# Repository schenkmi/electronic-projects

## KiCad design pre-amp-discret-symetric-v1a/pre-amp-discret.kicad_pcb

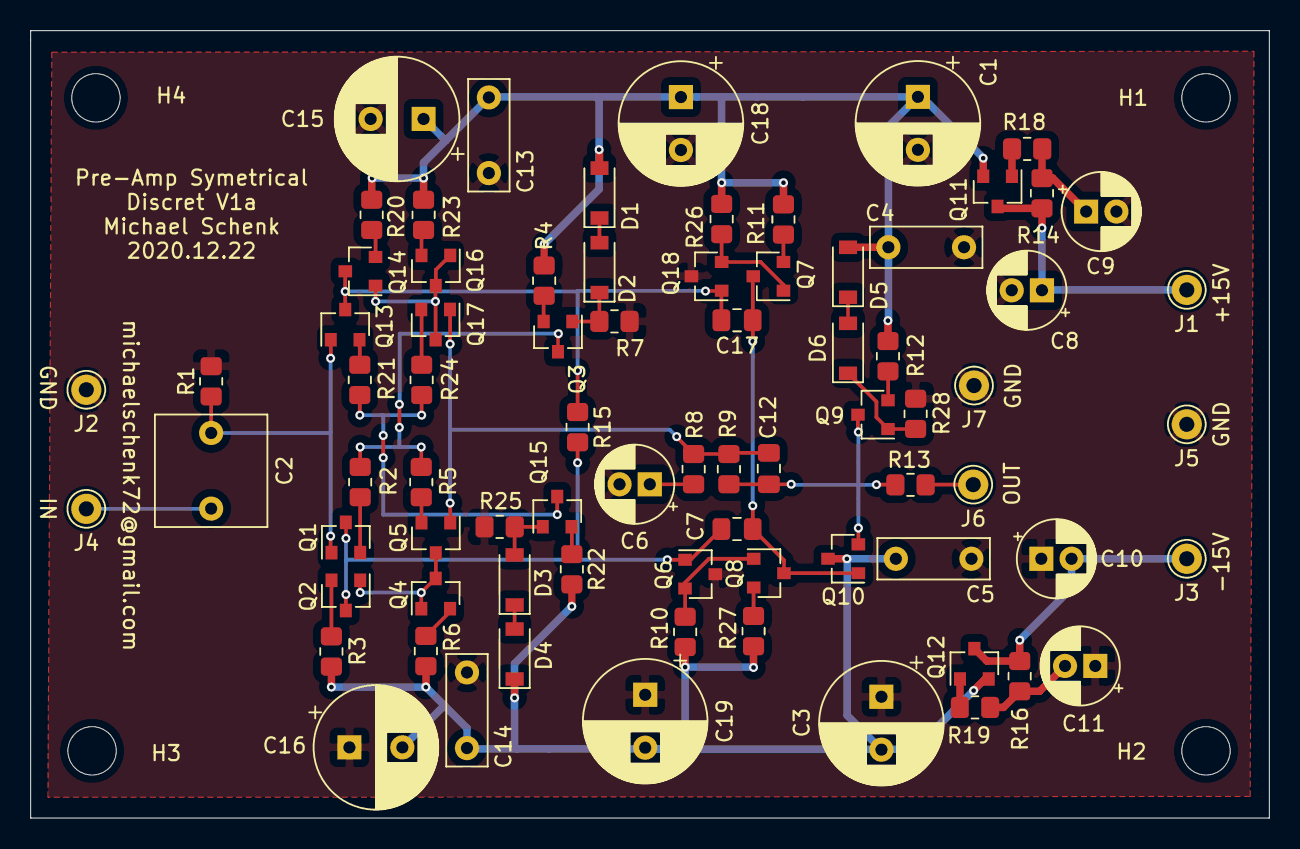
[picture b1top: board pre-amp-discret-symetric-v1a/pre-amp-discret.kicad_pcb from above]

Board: 2 copper layers, 81.9 x 52.1 mm, 81 parts (0 on the bottom side), 43 nets.

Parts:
C1, C3, C15, C16, C18, C19: 220uF; CP_Radial_D8.0mm_P3.50mm
C2: 2.2uF; C_Rect_L7.2mm_W7.2mm_P5.00mm_FKS2_FKP2_MKS2_MKP2
C4, C5, C13, C14: 100nF; C_Rect_L7.2mm_W2.5mm_P5.00mm_FKS2_FKP2_MKS2_MKP2
C6, C8, C9, C10, C11: 100uF; CP_Radial_D5.0mm_P2.00mm
C7, C17: 1nF; C_0805_2012Metric_Pad1.18x1.45mm_HandSolder
C12: 4.7pF; C_0805_2012Metric_Pad1.18x1.45mm_HandSolder
D1, D2, D3, D4, D5, D6: 1N4148W; D_SOD-123
H1, H2, H3, H4: MountingHole; MountingHole_3.2mm_M3
J1, J2, J3, J4, J5, J6, J7: Conn_01x01; Pin_D1.0mm_L10.0mm
Q1, Q3, Q5, Q7, Q9, Q10, Q12, Q14, Q16, Q18: BC860C; SOT-23
Q2, Q4, Q6, Q8, Q11, Q13, Q15, Q17: BC850C; SOT-23
R1, R8, R9: 22k; R_0805_2012Metric_Pad1.20x1.40mm_HandSolder
R2, R5, R12, R18, R19, R21, R24: 100R; R_0805_2012Metric_Pad1.20x1.40mm_HandSolder
R3, R6, R20, R23: 68R; R_0805_2012Metric_Pad1.20x1.40mm_HandSolder
R4, R22: 150R; R_0805_2012Metric_Pad1.20x1.40mm_HandSolder
R7, R14, R16, R25, R28: 10k; R_0805_2012Metric_Pad1.20x1.40mm_HandSolder
R10, R26: 2k2; R_0805_2012Metric_Pad1.20x1.40mm_HandSolder
R11, R27: 39R; R_0805_2012Metric_Pad1.20x1.40mm_HandSolder
R13: 47R; R_0805_2012Metric_Pad1.20x1.40mm_HandSolder
R15: 250k; R_0805_2012Metric_Pad1.20x1.40mm_HandSolder

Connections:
+15V: C1.1, C4.2, C13.2, C15.1, C18.1, D1.2, D5.2, Q11.2, R4.1, R11.1, R12.1, R20.1, R23.1, R26.1
-15V: C3.2, C5.1, C14.1, C16.2, C19.2, D4.1, Q10.3, Q12.2, R3.2, R6.2, R10.2, R22.2, R27.2
GND: C1.2, C3.1, C4.1, C5.2, C6.2, C8.2, C9.2, C10.1, C11.1, C13.1, C14.2, C15.2, C16.1, C18.2, C19.1, J2.1, J5.1, J7.1, Q6.3, Q18.3, R1.2, R7.2, R25.1, R28.2
unnamed: C2.1, Q1.1, Q13.1, R1.1
unnamed: C2.2, J4.1
unnamed: C6.1, R8.2
unnamed: C7.2, Q1.3, Q2.3, Q6.1, R15.2
unnamed: C8.1, J1.1, Q11.3, R14.2
unnamed: C9.1, R14.1, R18.1
unnamed: C10.2, J3.1, Q12.3, R16.2
unnamed: C11.2, R16.1, R19.1
unnamed: C12.1, Q9.3, Q10.2, R9.1, R13.2
unnamed: C12.2, Q5.1, Q17.1, R8.1, R9.2
unnamed: C7.1, C17.1, Q7.3, Q8.3, Q10.1
unnamed: C17.2, Q13.3, Q14.3, Q18.1, R15.1
unnamed: D1.1, D2.2
unnamed: D2.1, Q3.1, R7.1
unnamed: D3.1, D4.2
unnamed: D3.2, Q15.1, R25.2
unnamed: D5.1, D6.2
unnamed: D6.1, Q9.1, R28.1
unnamed: J6.1, R13.1
unnamed: Q1.2, R2.2
unnamed: Q2.1, Q4.1, Q4.3, Q5.3
unnamed: Q2.2, R3.1
unnamed: Q3.2, R4.2
unnamed: Q3.3, R2.1, R5.1
unnamed: Q4.2, R6.1
unnamed: Q5.2, R5.2
unnamed: Q6.2, Q8.1, R10.1
unnamed: Q7.2, R11.2
unnamed: Q8.2, R27.1
unnamed: Q9.2, R12.2
unnamed: Q11.1, R18.2
unnamed: Q12.1, R19.2
unnamed: Q13.2, R21.1
unnamed: Q14.1, Q16.1, Q16.3, Q17.3
unnamed: Q14.2, R20.2
unnamed: Q15.2, R22.1
unnamed: Q15.3, R21.2, R24.2
unnamed: Q16.2, R23.2
unnamed: Q17.2, R24.1
unnamed: Q7.1, Q18.2, R26.2

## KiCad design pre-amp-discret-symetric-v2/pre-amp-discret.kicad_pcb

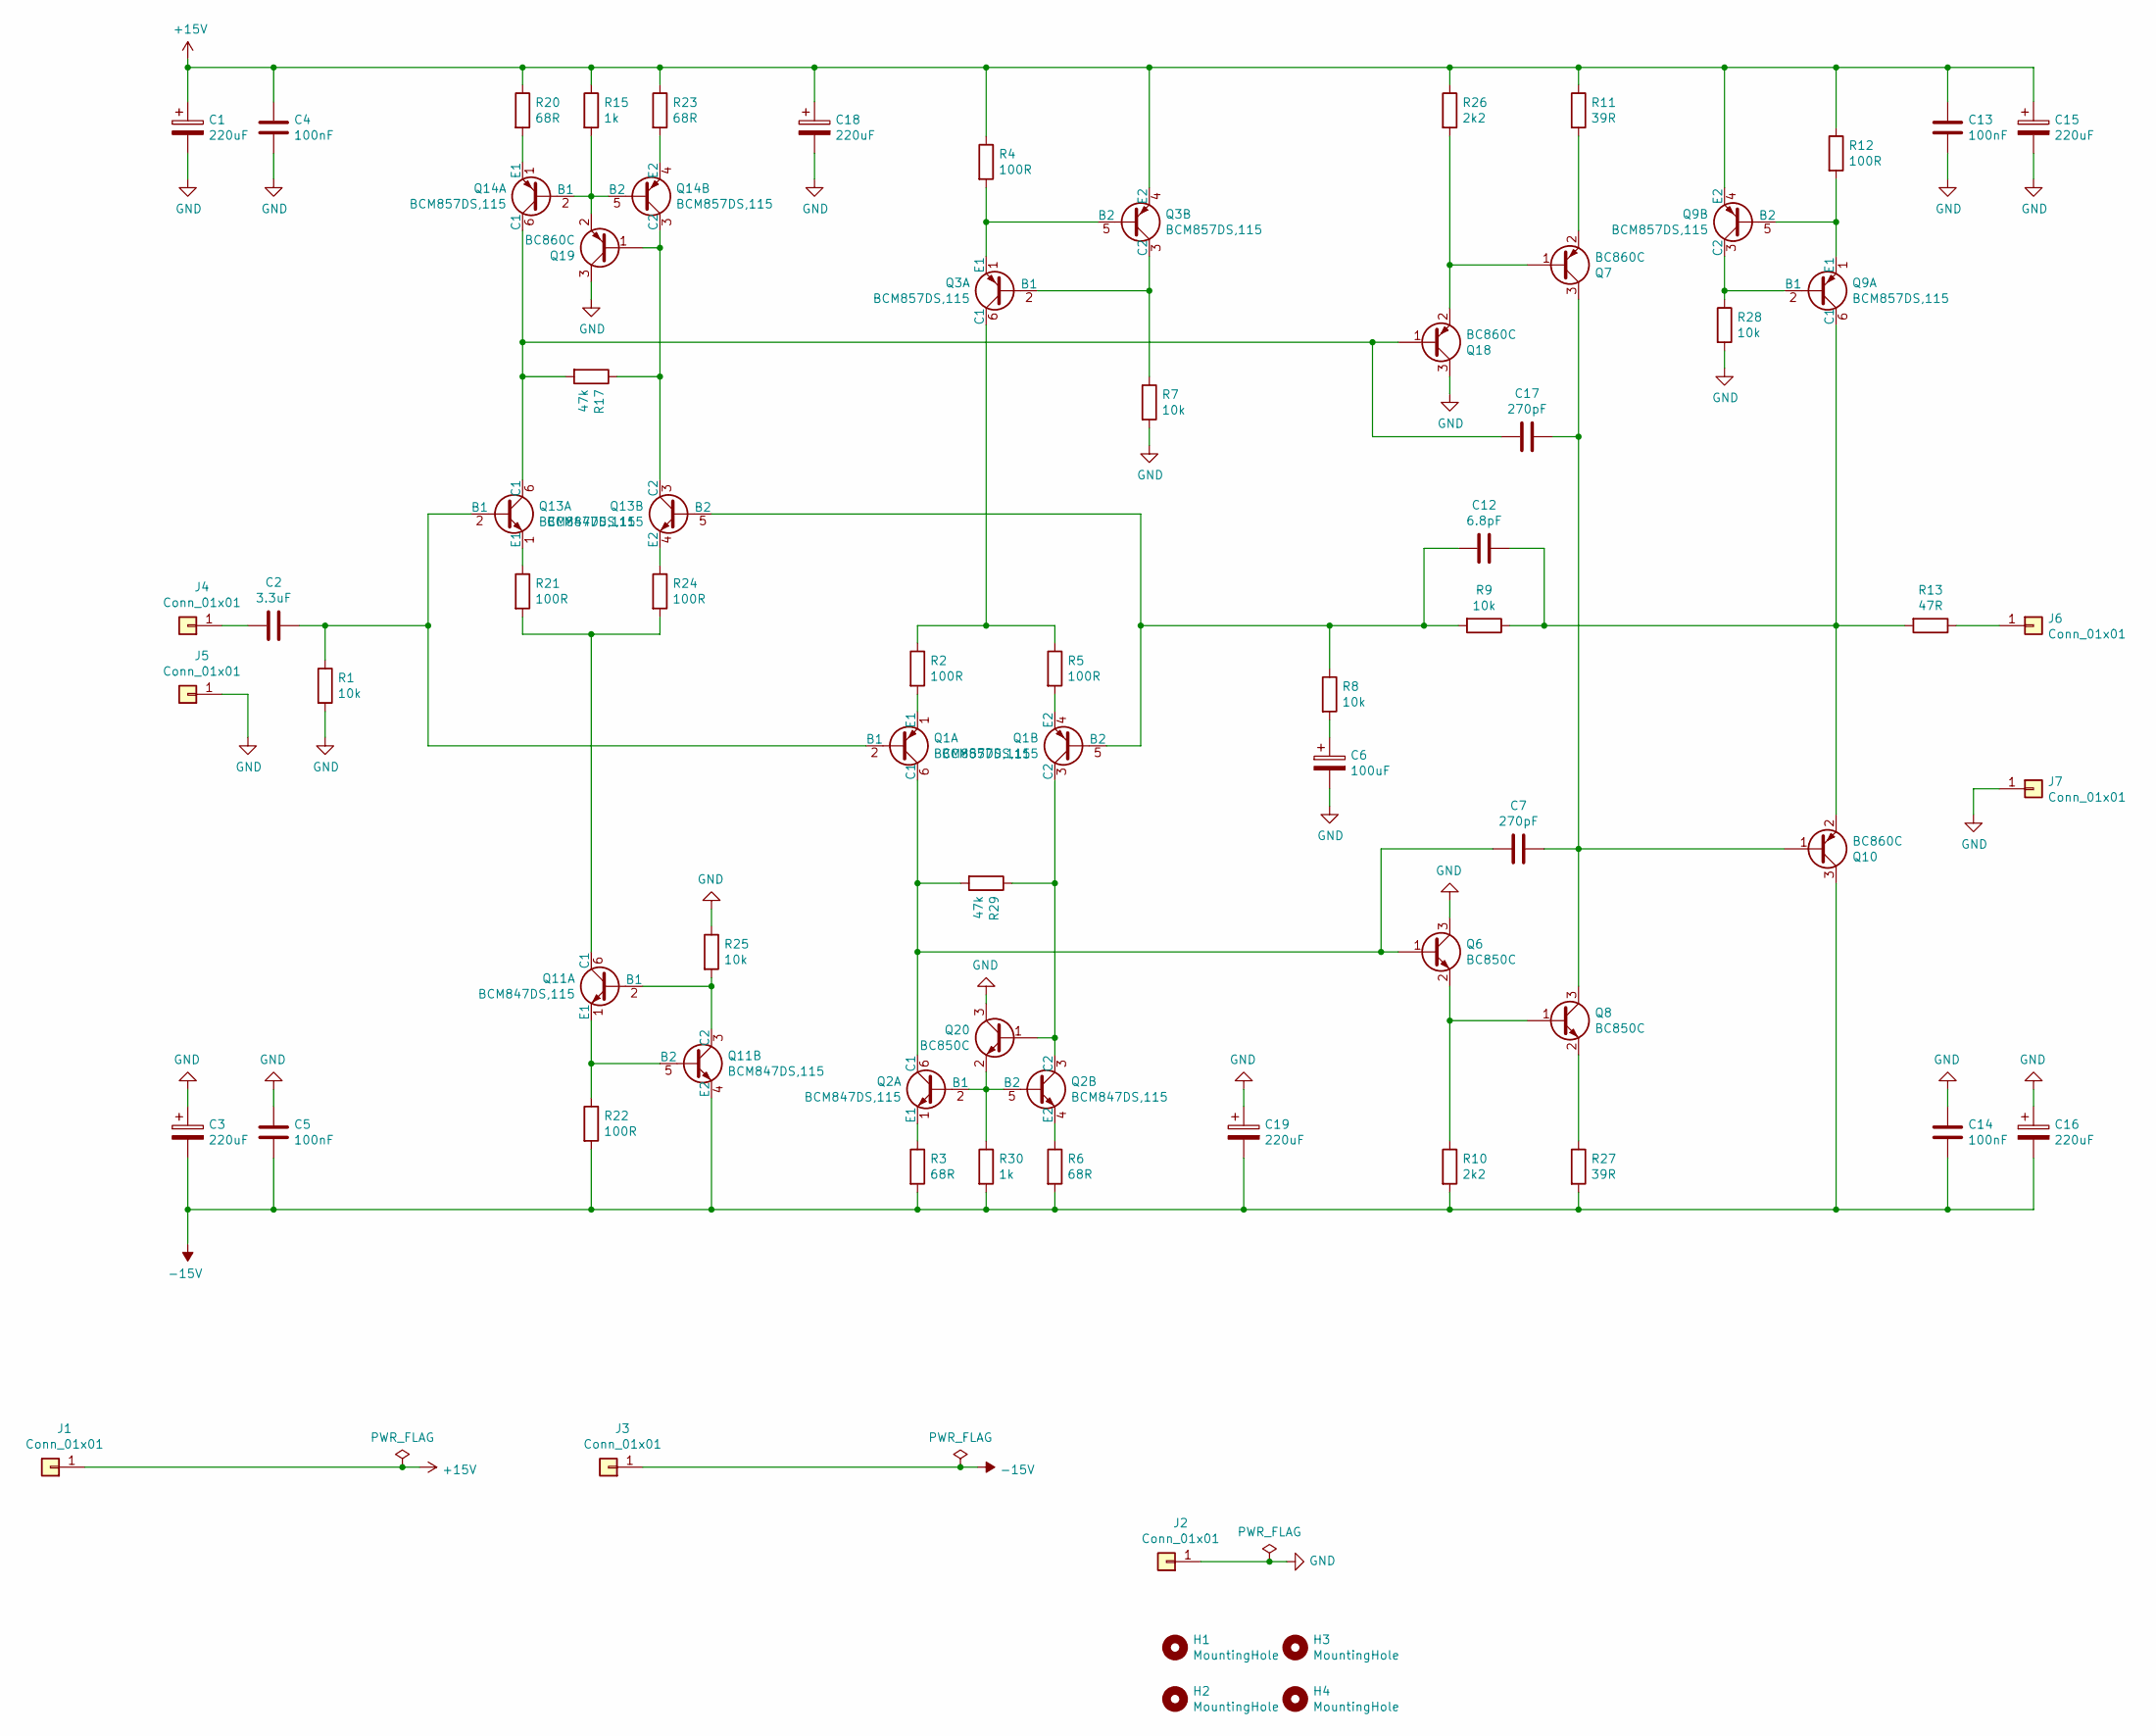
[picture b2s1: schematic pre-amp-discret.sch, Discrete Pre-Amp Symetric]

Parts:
C1, C3, C15, C16, C18, C19: 220uF; CP_Radial_D8.0mm_P3.50mm
C2: 3.3uF; C_Rect_L7.2mm_W7.2mm_P5.00mm_FKS2_FKP2_MKS2_MKP2
C4, C5, C13, C14: 100nF; C_Rect_L7.2mm_W2.5mm_P5.00mm_FKS2_FKP2_MKS2_MKP2
C6: 100uF; CP_Radial_D5.0mm_P2.00mm
C7, C17: 270pF; C_0805_2012Metric_Pad1.18x1.45mm_HandSolder
C12: 6.8pF; C_0805_2012Metric_Pad1.18x1.45mm_HandSolder
H1, H2, H3, H4: MountingHole; MountingHole_3.2mm_M3
J1, J2, J3, J4, J5, J6, J7: Conn_01x01; Pin_D1.0mm_L10.0mm
Q1, Q3, Q9, Q14: BCM857DS,115; SC-74-6_1.5x2.9mm_P0.95mm
Q2, Q11, Q13: BCM847DS,115; SC-74-6_1.5x2.9mm_P0.95mm
Q6, Q8, Q20: BC850C; SOT-23
Q7, Q10, Q18, Q19: BC860C; SOT-23
R1, R7, R8, R9, R25, R28: 10k; R_0805_2012Metric_Pad1.20x1.40mm_HandSolder
R2, R4, R5, R12, R21, R22, R24: 100R; R_0805_2012Metric_Pad1.20x1.40mm_HandSolder
R3, R6, R20, R23: 68R; R_0805_2012Metric_Pad1.20x1.40mm_HandSolder
R10, R26: 2k2; R_0805_2012Metric_Pad1.20x1.40mm_HandSolder
R11, R27: 39R; R_0805_2012Metric_Pad1.20x1.40mm_HandSolder
R13: 47R; R_0805_2012Metric_Pad1.20x1.40mm_HandSolder
R15, R30: 1k; R_0805_2012Metric_Pad1.20x1.40mm_HandSolder
R17, R29: 47k; R_0805_2012Metric_Pad1.20x1.40mm_HandSolder

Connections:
+15V: C1.1, C4.2, C13.2, C15.1, C18.1, J1.1, Q3.4 (E2), Q9.4 (E2), R4.1, R11.1, R12.1, R15.1, R20.1, R23.1, R26.1
-15V: C3.2, C5.1, C14.1, C16.2, C19.2, J3.1, Q10.3 (C), Q11.4 (E2), R3.2, R6.2, R10.2, R22.2, R27.2, R30.2
GND: C1.2, C3.1, C4.1, C5.2, C6.2, C13.1, C14.2, C15.2, C16.1, C18.2, C19.1, J2.1, J5.1, J7.1, Q6.3 (C), Q18.3 (C), Q19.3 (C), Q20.3 (C), R1.2, R7.2, R25.1, R28.2
unnamed: C2.1, Q1.2 (B1), Q13.2 (B1), R1.1
unnamed: C2.2, J4.1
unnamed: C6.1, R8.2
unnamed: C7.2, Q1.6 (C1), Q2.6 (C1), Q6.1 (B), R29.2
unnamed: C12.1, Q9.6 (C1), Q10.2 (E), R9.1, R13.2
unnamed: C12.2, Q1.5 (B2), Q13.5 (B2), R8.1, R9.2
unnamed: C7.1, C17.1, Q7.3 (C), Q8.3 (C), Q10.1 (B)
unnamed: C17.2, Q13.6 (C1), Q14.6 (C1), Q18.1 (B), R17.2
unnamed: J6.1, R13.1
unnamed: Q1.1 (E1), R2.2
unnamed: Q1.3 (C2), Q2.3 (C2), Q20.1 (B), R29.1
unnamed: Q1.4 (E2), R5.2
unnamed: Q2.1 (E1), R3.1
unnamed: Q2.2 (B1), Q2.5 (B2), Q20.2 (E), R30.1
unnamed: Q2.4 (E2), R6.1
unnamed: Q3.1 (E1), Q3.5 (B2), R4.2
unnamed: Q3.2 (B1), Q3.3 (C2), R7.1
unnamed: Q3.6 (C1), R2.1, R5.1
unnamed: Q6.2 (E), Q8.1 (B), R10.1
unnamed: Q7.2 (E), R11.2
unnamed: Q8.2 (E), R27.1
unnamed: Q9.1 (E1), Q9.5 (B2), R12.2
unnamed: Q9.2 (B1), Q9.3 (C2), R28.1
unnamed: Q11.1 (E1), Q11.5 (B2), R22.1
unnamed: Q11.2 (B1), Q11.3 (C2), R25.2
unnamed: Q11.6 (C1), R21.2, R24.2
unnamed: Q13.1 (E1), R21.1
unnamed: Q13.3 (C2), Q14.3 (C2), Q19.1 (B), R17.1
unnamed: Q13.4 (E2), R24.1
unnamed: Q14.1 (E1), R20.2
unnamed: Q14.2 (B1), Q14.5 (B2), Q19.2 (E), R15.2
unnamed: Q14.4 (E2), R23.2
unnamed: Q7.1 (B), Q18.2 (E), R26.2

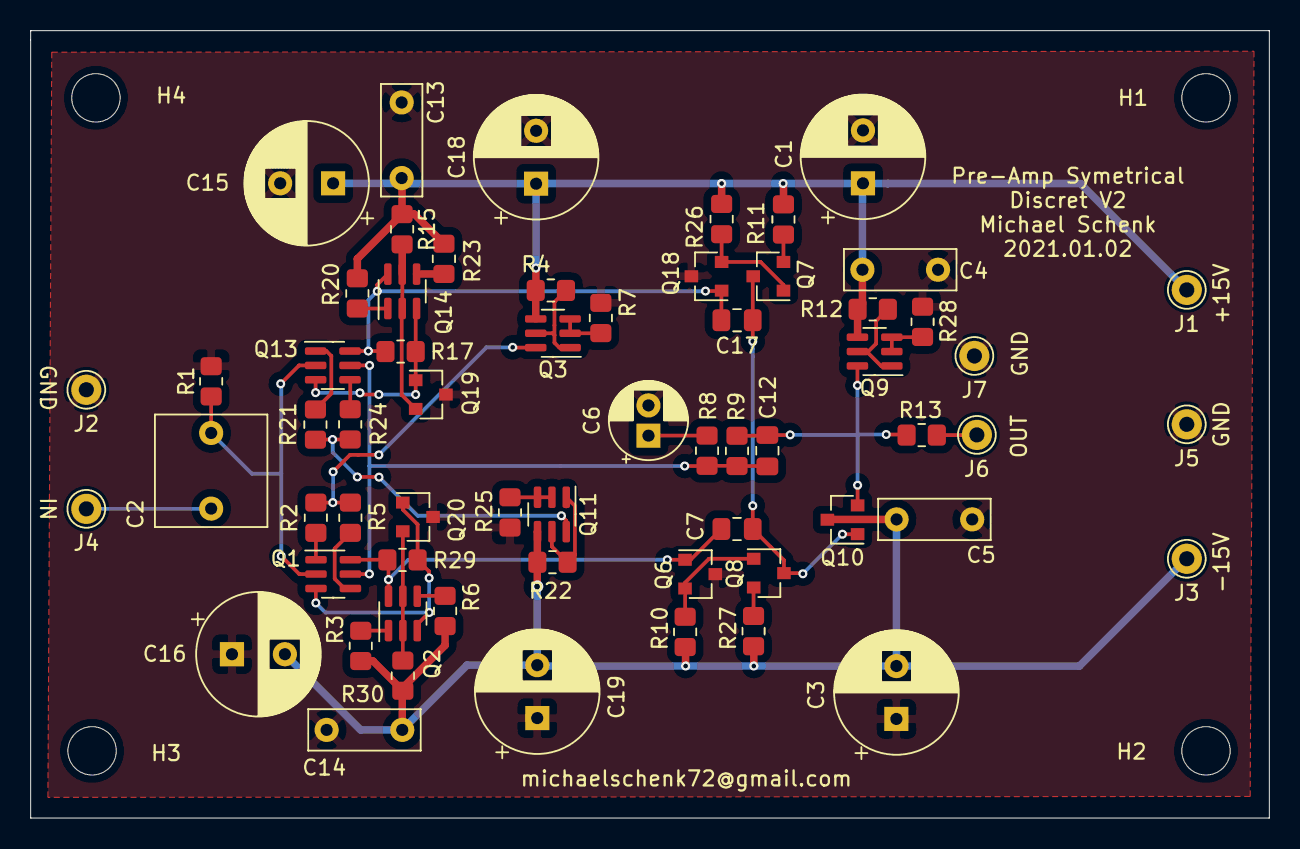
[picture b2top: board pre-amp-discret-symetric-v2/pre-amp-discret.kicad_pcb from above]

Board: 2 copper layers, 81.9 x 52.1 mm, 66 parts (0 on the bottom side), 36 nets.
